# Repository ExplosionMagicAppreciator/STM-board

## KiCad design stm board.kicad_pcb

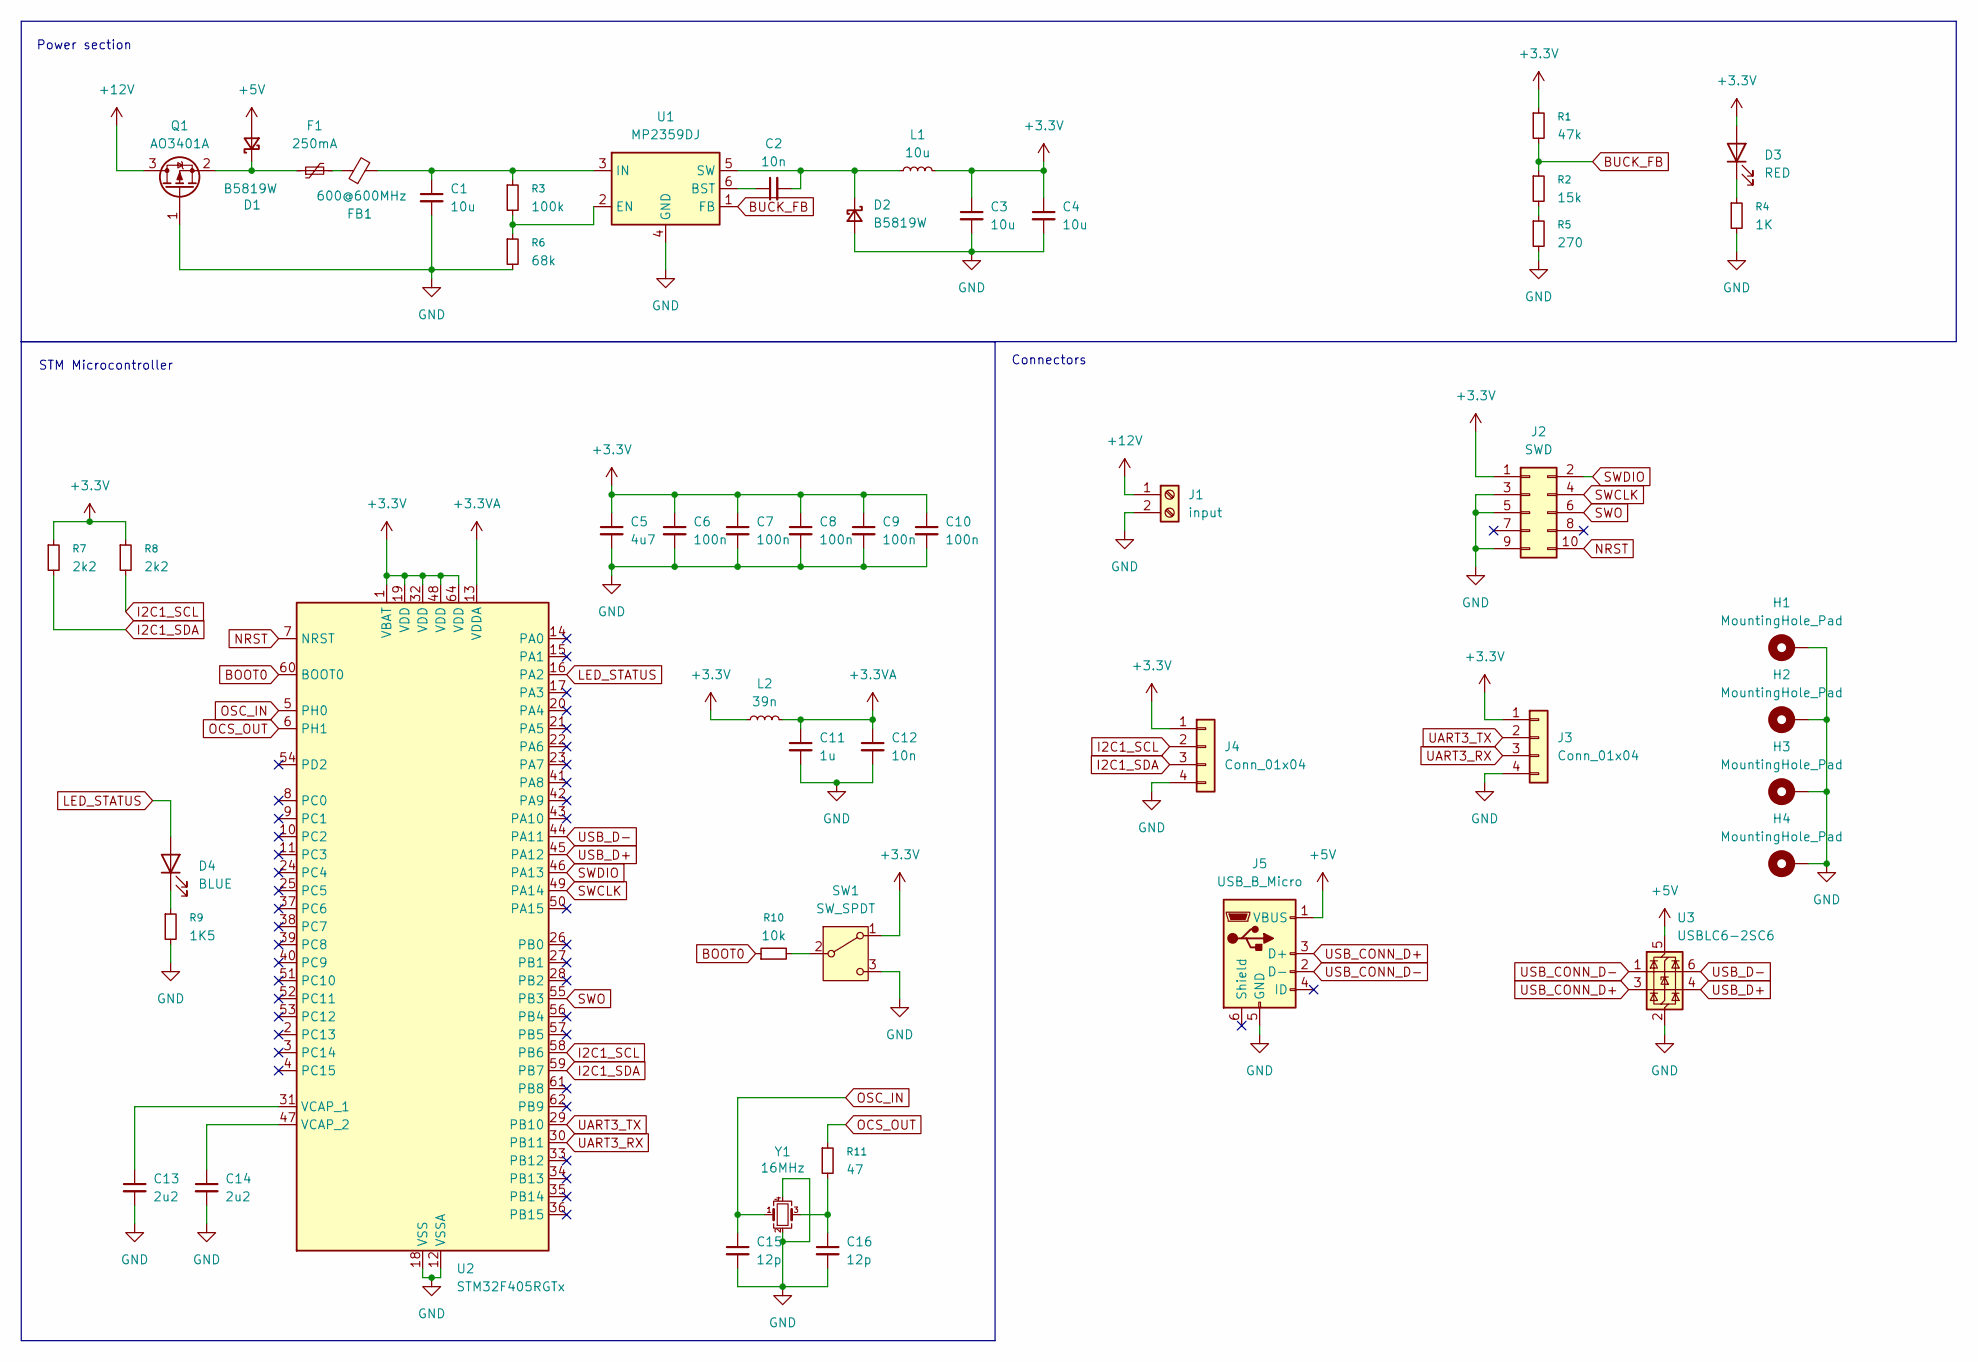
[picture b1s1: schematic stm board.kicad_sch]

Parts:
C1, C3, C4: 10u; C_1206_3216Metric
C2: 10n; C_0603_1608Metric
C5: 4u7; C_0603_1608Metric
C6, C7, C8, C9, C10: 100n; C_0402_1005Metric
C11: 1u; C_0402_1005Metric
C12: 10n; C_0402_1005Metric
C13, C14: 2u2; C_0201_0603Metric
C15, C16: 12p; C_0402_1005Metric
D1, D2: B5819W; D_SOD-123
D3: RED; LED_0201_0603Metric
D4: BLUE; LED_0201_0603Metric
F1: 250mA; Fuse_1206_3216Metric
FB1: 600@600MHz; L_0805_2012Metric
H1, H2, H3, H4: MountingHole_Pad; MountingHole_2.7mm_Pad_Via
J1: input; TerminalBlock_4Ucon_1x02_P3.50mm_Horizontal
J2: SWD; PinHeader_2x05_P1.00mm_Vertical
J3, J4: Conn_01x04; Molex_PicoBlade_53048-0410_1x04_P1.25mm_Horizontal
J5: USB_B_Micro; USB_Micro-B_GCT_USB3076-30-A
L1: 10u; L_Sunlord_MWSA0518S
L2: 39n; L_0402_1005Metric
Q1: AO3401A; SOT-23
R1: 47k; R_0603_1608Metric
R2: 15k; R_0603_1608Metric
R3: 100k; R_0603_1608Metric
R4: 1K; R_0603_1608Metric
R5: 270; R_0603_1608Metric
R6: 68k; R_0603_1608Metric
R7, R8: 2k2; R_0402_1005Metric
R9: 1K5; R_0603_1608Metric
R10: 10k; R_0402_1005Metric
R11: 47; R_0402_1005Metric
SW1: SW_SPDT; SW_SPDT_PCM12
U1: MP2359DJ; SOT-23-6
U2: STM32F405RGTx; LQFP-64_10x10mm_P0.5mm
U3: USBLC6-2SC6; SOT-23-6
Y1: 16MHz; Crystal_SMD_3225-4Pin_3.2x2.5mm

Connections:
+3.3V: C3.1, C4.1, C5.1, C6.1, C7.1, C8.1, C9.1, C10.1, D3.2 (A), J2.1, J3.1, J4.1, L1.2, L2.1, R1.1, R7.1, R8.1, SW1.1 (A), U2.1 (VBAT), U2.19 (VDD), U2.32 (VDD), U2.48 (VDD), U2.64 (VDD)
+3.3VA: C11.1, C12.1, L2.2, U2.13 (VDDA)
+5V: D1.2 (A), J5.1 (VBUS), U3.5 (VBUS)
+12V: J1.1, Q1.3 (D)
BOOT0: R10.1, U2.60 (BOOT0)
BUCK_FB: R1.2, R2.1, U1.1 (FB)
GND: C1.2, C3.2, C4.2, C5.2, C6.2, C7.2, C8.2, C9.2, C10.2, C11.2, C12.2, C13.2, C14.2, C15.2, C16.2, D2.2 (A), H1.1, H2.1, H3.1, H4.1, J1.2, J2.3, J2.5, J2.9, J3.4, J4.4, J5.5 (GND), Q1.1 (G), R4.2, R5.2, R6.2, R9.2, SW1.3 (C), U1.4 (GND), U2.12 (VSSA), U2.18 (VSS), U2.63 (VSS), U3.2 (GND), Y1.2, Y1.4
I2C1_SCL: J4.2, R8.2, U2.58 (PB6)
I2C1_SDA: J4.3, R7.2, U2.59 (PB7)
LED_STATUS: D4.2 (A), U2.16 (PA2)
NRST: J2.10, U2.7 (NRST)
unnamed: C16.1, R11.2, Y1.3
unnamed: D1.1 (K), F1.1, Q1.2 (S)
unnamed: C2.2, D2.1 (K), L1.1, U1.5 (SW)
unnamed: D3.1 (K), R4.1
unnamed: D4.1 (K), R9.1
unnamed: F1.2, FB1.1
unnamed: R2.2, R5.1
unnamed: R10.2, SW1.2 (B)
unnamed: C2.1, U1.6 (BST)
unnamed: R3.2, R6.1, U1.2 (EN)
unnamed: C1.1, FB1.2, R3.1, U1.3 (IN)
unnamed: C13.1, U2.31 (VCAP_1)
unnamed: C14.1, U2.47 (VCAP_2)
OCS_OUT: R11.1, U2.6 (PH1)
OSC_IN: C15.1, U2.5 (PH0), Y1.1
SWCLK: J2.4, U2.49 (PA14)
SWDIO: J2.2, U2.46 (PA13)
SWO: J2.6, U2.55 (PB3)
UART3_RX: J3.3, U2.30 (PB11)
UART3_TX: J3.2, U2.29 (PB10)
USB_CONN_D+: J5.3 (D+), U3.3 (I/O2)
USB_CONN_D-: J5.2 (D-), U3.1 (I/O1)
USB_D+: U2.45 (PA12), U3.4 (I/O2)
USB_D-: U2.44 (PA11), U3.6 (I/O1)

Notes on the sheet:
Power section
Connectors
STM Microcontroller

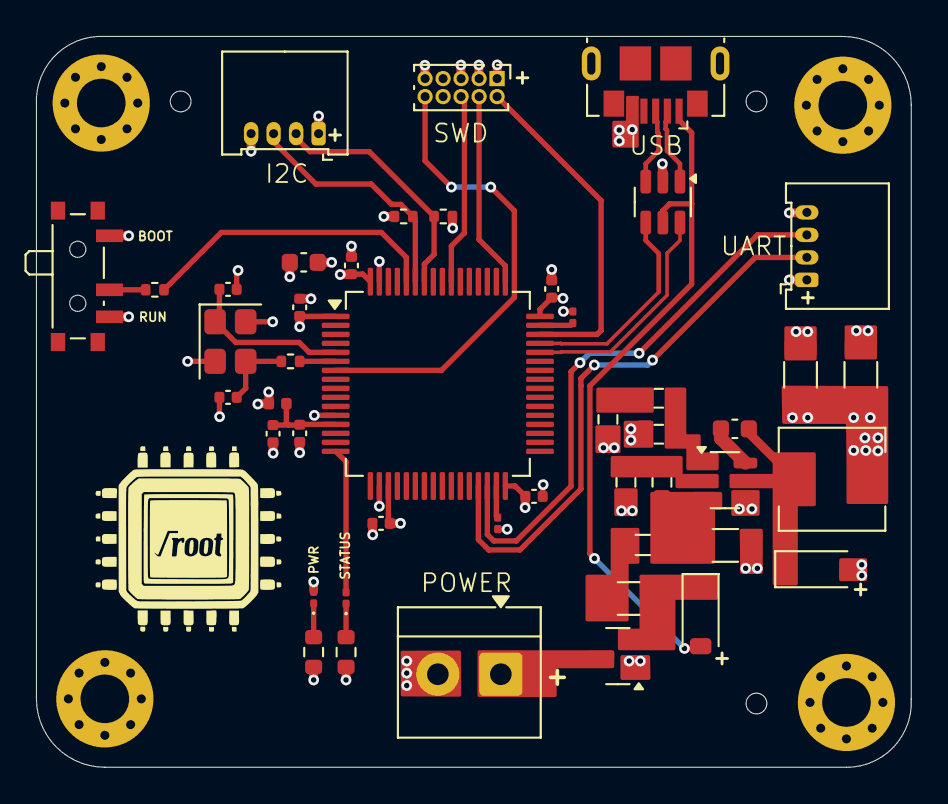
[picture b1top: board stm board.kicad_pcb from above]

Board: 4 copper layers, 48.6 x 40.6 mm, 50 parts (0 on the bottom side), 35 nets.

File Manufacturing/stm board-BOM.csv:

"Reference","Qty","Value","DNP","Exclude from BOM","Exclude from Board","Footprint","Datasheet"
"C1,C3,C4","3","10u","","","","Capacitor_SMD:C_1206_3216Metric","~"
"C2","1","10n","","","","Capacitor_SMD:C_0603_1608Metric","~"
"C5","1","4u7","","","","Capacitor_SMD:C_0603_1608Metric","~"
"C6,C7,C8,C9,C10","5","100n","","","","Capacitor_SMD:C_0402_1005Metric","~"
"C11","1","1u","","","","Capacitor_SMD:C_0402_1005Metric","~"
"C12","1","10n","","","","Capacitor_SMD:C_0402_1005Metric","~"
"C13,C14","2","2u2","","","","Capacitor_SMD:C_0201_0603Metric","~"
"C15,C16","2","12p","","","","Capacitor_SMD:C_0402_1005Metric","~"
"D1,D2","2","B5819W","","","","Diode_SMD:D_SOD-123","~"
"D3","1","RED","","","","LED_SMD:LED_0201_0603Metric","~"
"D4","1","BLUE","","","","LED_SMD:LED_0201_0603Metric","~"
"F1","1","250mA","","","","Fuse:Fuse_1206_3216Metric","~"
"FB1","1","600@600MHz","","","","Inductor_SMD:L_0805_2012Metric","~"
"H1,H2,H3,H4","4","MountingHole_Pad","","Excluded from BOM","","MountingHole:MountingHole_2.7mm_Pad_Via","~"
"J1","1","input","","","","TerminalBlock_4Ucon:TerminalBlock_4Ucon_1x02_P3.50mm_Horizontal","~"
"J2","1","SWD","","","","Connector_PinHeader_1.00mm:PinHeader_2x05_P1.00mm_Vertical","~"
"J3,J4","2","Conn_01x04","","","","Connector_Molex:Molex_PicoBlade_53048-0410_1x04_P1.25mm_Horizontal","~"
"J5","1","USB_B_Micro","","","","Connector_USB:USB_Micro-B_GCT_USB3076-30-A","~"
"L1","1","10u","","","","Inductor_SMD:L_Sunlord_MWSA0518S","~"
"L2","1","39n","","","","Inductor_SMD:L_0402_1005Metric","~"
"Q1","1","AO3401A","","","","Package_TO_SOT_SMD:SOT-23","http://www.aosmd.com/pdfs/datasheet/AO3401A.pdf"
"R1","1","47k","","","","Resistor_SMD:R_0603_1608Metric","~"
"R2","1","15k","","","","Resistor_SMD:R_0603_1608Metric","~"
"R3","1","100k","","","","Resistor_SMD:R_0603_1608Metric","~"
"R4","1","1K","","","","Resistor_SMD:R_0603_1608Metric","~"
"R5","1","270","","","","Resistor_SMD:R_0603_1608Metric","~"
"R6","1","68k","","","","Resistor_SMD:R_0603_1608Metric","~"
"R7,R8","2","2k2","","","","Resistor_SMD:R_0402_1005Metric","~"
"R9","1","1K5","","","","Resistor_SMD:R_0603_1608Metric","~"
"R10","1","10k","","","","Resistor_SMD:R_0402_1005Metric","~"
"R11","1","47","","","","Resistor_SMD:R_0402_1005Metric","~"
"SW1","1","SW_SPDT","","","","Button_Switch_SMD:SW_SPDT_PCM12","~"
"U1","1","MP2359DJ","","","","Package_TO_SOT_SMD:SOT-23-6",""
"U2","1","STM32F405RGTx","","","","Package_QFP:LQFP-64_10x10mm_P0.5mm","https://www.st.com/resource/en/datasheet/stm32f405rg.pdf"
"U3","1","USBLC6-2SC6","","","","Package_TO_SOT_SMD:SOT-23-6","https://www.st.com/resource/en/datasheet/usblc6-2.pdf"
"Y1","1","16MHz","","","","Crystal:Crystal_SMD_3225-4Pin_3.2x2.5mm","~"
